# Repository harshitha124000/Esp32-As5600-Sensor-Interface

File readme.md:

esp32-As5600-sensor schematic
The ESP32 is a powerful, low-cost Wi-Fi and Bluetooth microcontroller designed for IoT applications.it is powerd by a 3.3v supply.The assign as follows:DIR,SCL,SDA,and PWM for the AS5600 function
AMS117use to populor linear voltage regulator and provide the fixed output volatge  from the higher input voltage 
AS5600, a contactless magnetic rotary position sensor, involves careful attention to power supply, communication lines, and layout considerations.
I have use voltage convertor to regulate the power from 24v to 5v.

This is interface design of the esp32-as5600-sensor front boad design 
Microcontroller/Esp32 : Position centrally for optimal signal routing and minimize trace lengths.
Power Management: Cluster power components near power input for efficient distribution.
Connectors: Place connectors on edges or corners for easy access and to accommodate external connections.
Peripherals: Arrange peripherals as5600-sensor based on signal flow and proximity to the microcontroller

back board design of the esp32-as5600-sensor 
 Use silkscreen to label components, connectors, and critical signals for easy identification during assembly and troubleshooting.
Component Designators: Clearly mark component designators (R1, C2, IC1, etc.) to aid in assembly and repair.
Design power distribution carefully to ensure stable voltage levels across the board.
 Place decoupling capacitors close to power pins of ICs to filter out noise and stabilize voltage.
 Ensure traces and vias can handle the current requirements without excessive heating.

These are industry-standard files that contain all the necessary information for PCB fabrication. 
Non-conductive ink applied on top of the solder mask for component labels, polarity markings, and other visual indicators. 
The Gerber files dictate the placement and content of silkscreen markings.
They include layers for copper traces, solder mask, silkscreen, drill files, and sometimes assembly data.
The base material (often FR-2 fiberglass) with copper layers laminated together according to the stack-up specified in the Gerber files.
The conductive pathways (traces) and copper pours specified in the Gerber files determine the electrical connectivity and grounding of the PCB.

 Gerber files include drill locations and sizes for vias and mounting holes
 Small holes filled with conductive material to connect copper layers. They enable routing of signals between different layers of the PCB.
After assembly, a surface finish Hot Air Solder Leveling, ENIG - Electroless Nickel Immersion Gold, etc is applied to ensure solderability and protect the PCB

 Manufacturers often perform automated electrical tests to verify connectivity and functionality of the PCB.
IVisual inspection and automated optical inspection (AOI) ensure that the PCB meets design specifications and quality standards.
PCBs are separated from the panel and may undergo additional cutting or routing to remove excess material.

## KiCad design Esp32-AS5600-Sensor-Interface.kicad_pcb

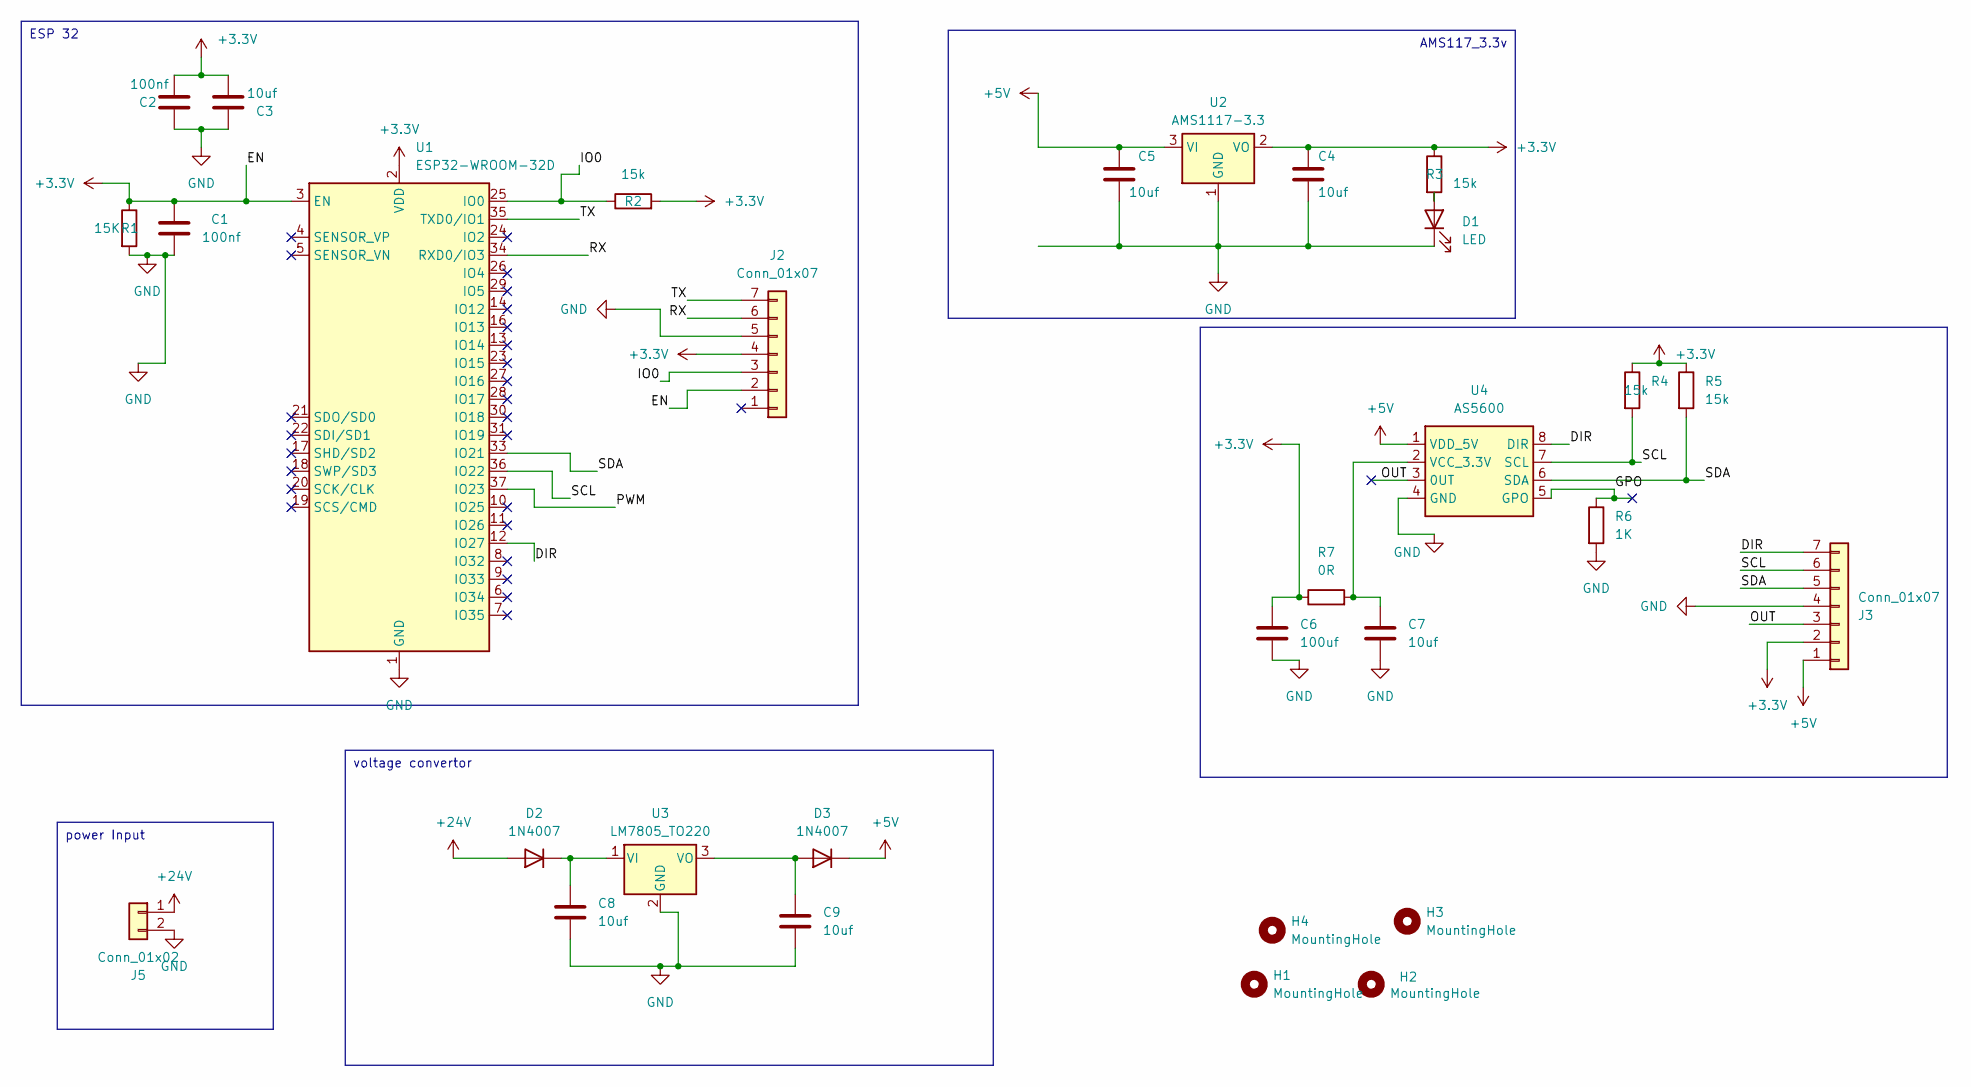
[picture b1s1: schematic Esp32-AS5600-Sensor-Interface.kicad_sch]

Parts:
C1, C2: 100nf; C_1206_3216Metric_Pad1.33x1.80mm_HandSolder
C3, C4, C5, C7, C8, C9: 10uf; C_1206_3216Metric_Pad1.33x1.80mm_HandSolder
C6: 100uf; C_1206_3216Metric_Pad1.33x1.80mm_HandSolder
D1: LED; LED_1206_3216Metric_Pad1.42x1.75mm_HandSolder
D2, D3: 1N4007; D_1206_3216Metric_Pad1.42x1.75mm_HandSolder
H1, H2, H3, H4: MountingHole; MountingHole_4.3mm_M4
J2, J3: Conn_01x07; JST_XH_B7B-XH-A_1x07_P2.50mm_Vertical
J5: Conn_01x02; TerminalBlock_bornier-2_P5.08mm
R1: 15K; R_1206_3216Metric_Pad1.30x1.75mm_HandSolder
R2, R3, R4, R5: 15k; R_1206_3216Metric_Pad1.30x1.75mm_HandSolder
R6: 1K; R_1206_3216Metric_Pad1.30x1.75mm_HandSolder
R7: 0R; R_1206_3216Metric_Pad1.30x1.75mm_HandSolder
U1: ESP32-WROOM-32D
U2: AMS1117-3.3; SOT-223-3_TabPin2
U3: LM7805_TO220; TO-263-2
U4: AS5600; MSOP-8_3x3mm_P0.65mm

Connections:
+3.3V: C1.1, C2.1, C3.1, C4.1, C6.1, J2.2, J2.4, J3.2, R1.1, R2.2, R3.1, R4.1, R5.1, R7.1, U1.2 (VDD), U1.3 (EN), U2.2 (VO)
+5V: C5.1, D3.1 (K), J3.1, U2.3 (VI), U4.1 (VDD_5V)
+24V: D2.2 (A), J5.1
/DIR: J3.7, U1.12 (IO27), U4.8 (DIR)
/GPO: R6.1, U4.5 (GPO)
/IO0: J2.3, R2.1, U1.25 (IO0)
/OUT: J3.3, U4.3 (0UT)
/PWM: U1.37 (IO23)
/RX: J2.6, U1.34 (RXD0/IO3)
/SCL: J3.6, R4.2, U1.36 (IO22), U4.7 (SCL)
/SDA: J3.5, R5.2, U1.33 (IO21), U4.6 (SDA)
/TX: J2.7, U1.35 (TXD0/IO1)
GND: C1.2, C2.2, C3.2, C4.2, C5.2, C6.2, C7.2, C8.2, C9.2, D1.1 (K), J2.5, J3.4, J5.2, R1.2, R6.2, U1.1 (GND), U1.15 (GND), U1.38 (GND), U1.39 (GND), U2.1 (GND), U3.2 (GND), U4.4 (GND)
unnamed: D1.2 (A), R3.2
unnamed: C8.1, D2.1 (K), U3.1 (VI)
unnamed: C9.1, D3.2 (A), U3.3 (VO)
unnamed: C7.1, R7.2, U4.2 (VCC_3.3V)

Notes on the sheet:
power Input
voltage convertor
AMS117_3.3v
ESP 32

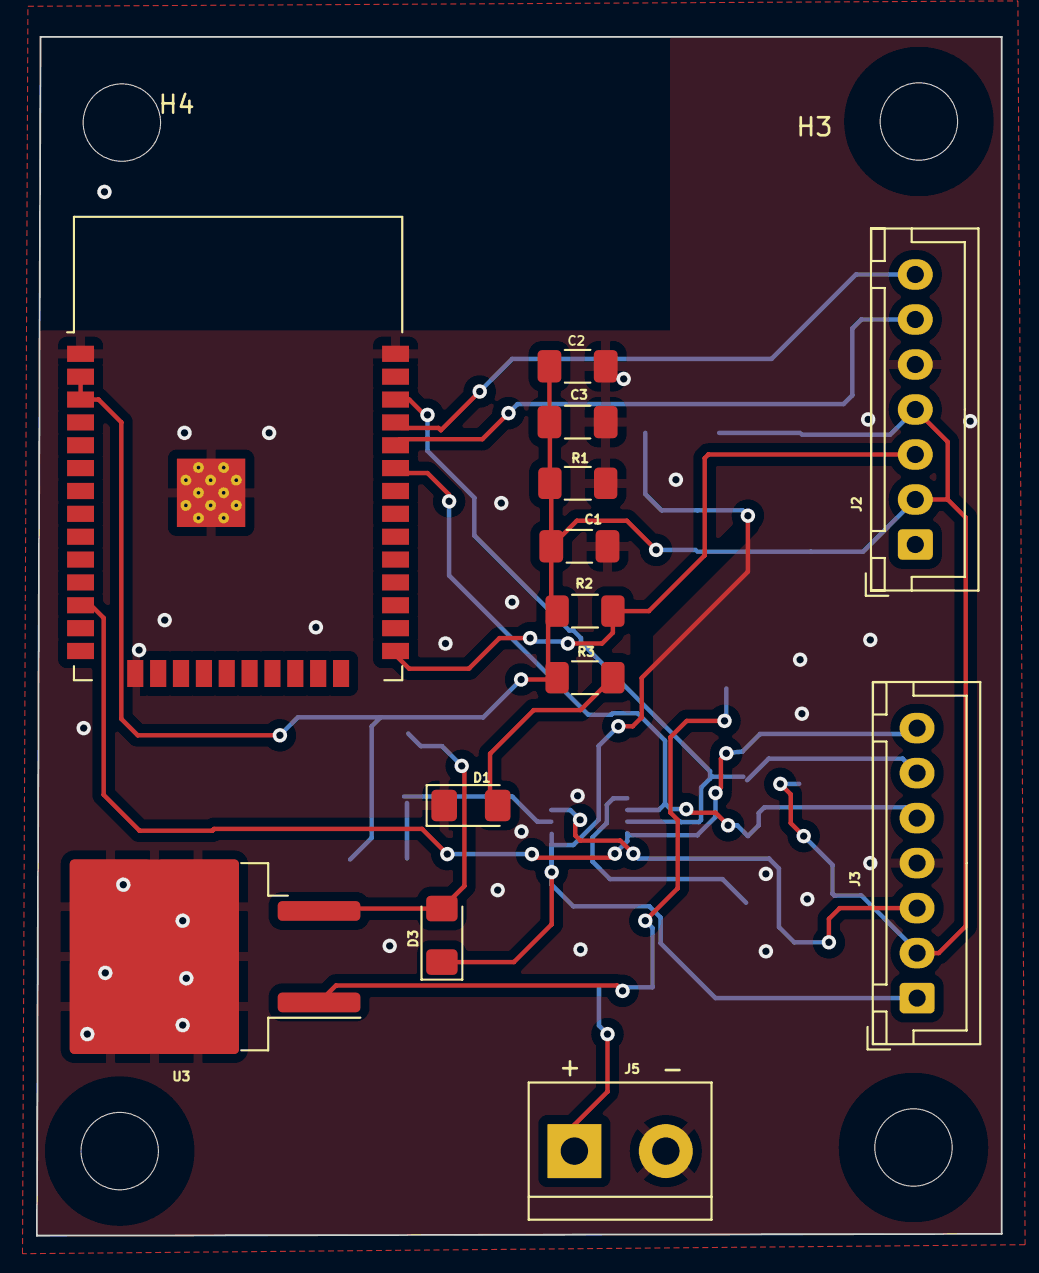
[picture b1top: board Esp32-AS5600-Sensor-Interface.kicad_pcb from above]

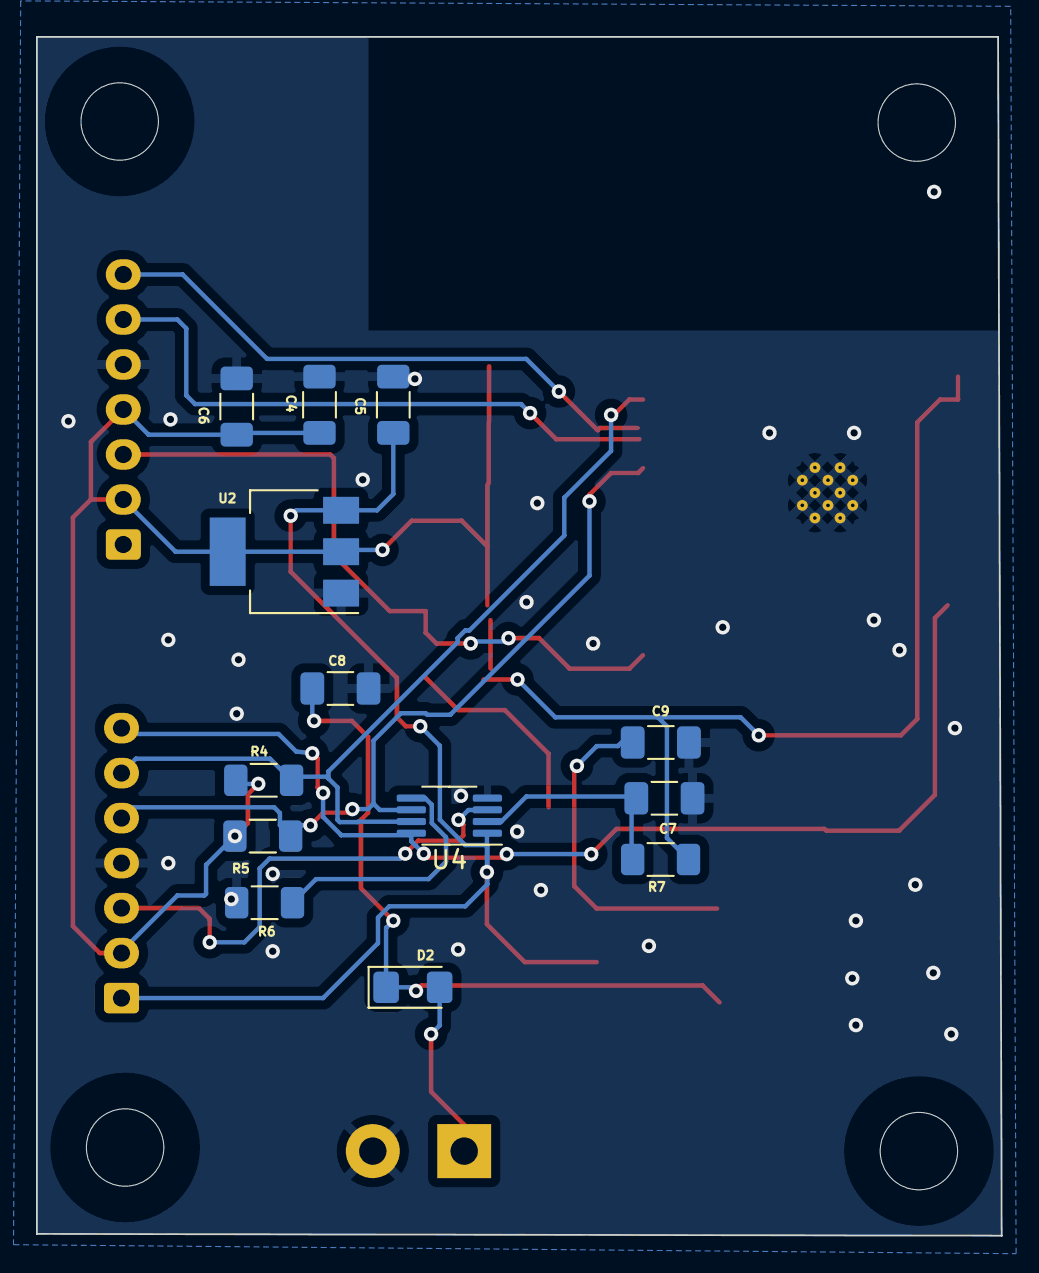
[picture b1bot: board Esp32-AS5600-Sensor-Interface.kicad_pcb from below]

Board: 2 copper layers, 53.6 x 66.6 mm, 30 parts (13 on the bottom side), 16 nets.

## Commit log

2024-05-28 first complte design
2024-05-28 add sch images
2024-06-10 schematic
2024-06-18 update
    update
